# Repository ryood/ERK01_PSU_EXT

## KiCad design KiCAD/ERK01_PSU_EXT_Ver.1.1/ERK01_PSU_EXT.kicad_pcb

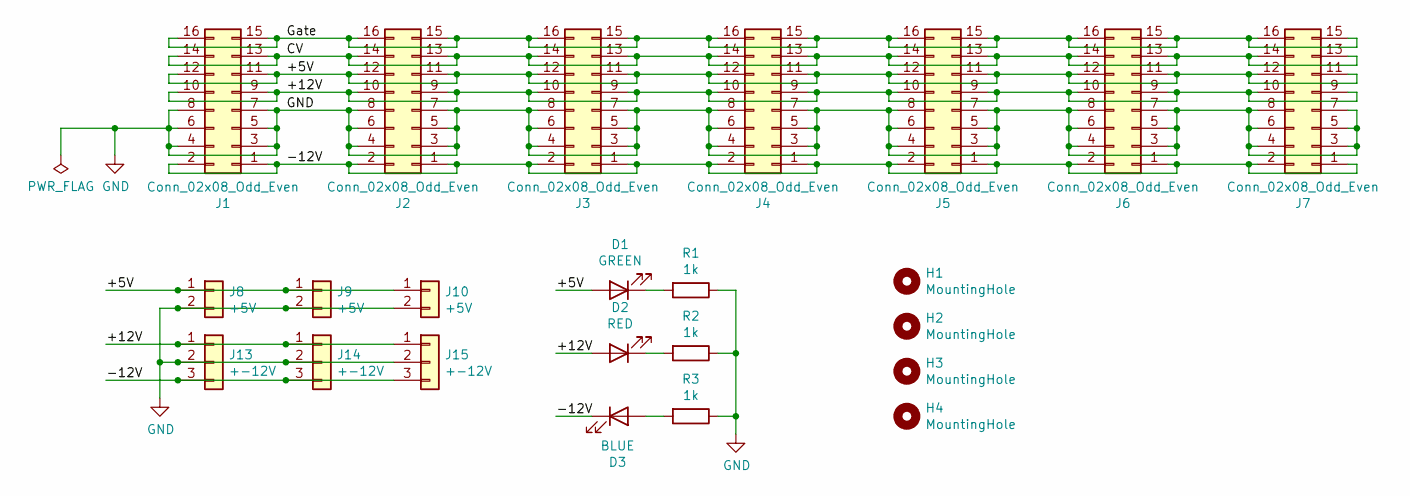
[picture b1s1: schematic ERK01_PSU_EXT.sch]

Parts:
D1: GREEN; LED_D3.0mm
D2: RED; LED_D3.0mm
D3: BLUE; LED_D3.0mm
H1, H2, H3, H4: MountingHole; MountingHole_3.2mm_M3
J1, J2, J3, J4, J5, J6, J7: Conn_02x08_Odd_Even; IDC-Header_2x08_P2.54mm_Vertical
J8, J9, J10: +5V; JST_XH_B2B-XH-A_1x02_P2.50mm_Vertical
J13, J14, J15: +-12V; JST_XH_B3B-XH-A_1x03_P2.50mm_Vertical
R1, R2, R3: 1k; R_Axial_DIN0207_L6.3mm_D2.5mm_P7.62mm_Horizontal

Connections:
/+5V: D1.2 (A), J1.11, J1.12, J2.11, J2.12, J3.11, J3.12, J4.11, J4.12, J5.11, J5.12, J6.11, J6.12, J7.11, J7.12, J8.1, J9.1, J10.1
/+12V: D2.2 (A), J1.9, J1.10, J2.9, J2.10, J3.9, J3.10, J4.9, J4.10, J5.9, J5.10, J6.9, J6.10, J7.9, J7.10, J13.1, J14.1, J15.1
/-12V: D3.1 (K), J1.1, J1.2, J2.1, J2.2, J3.1, J3.2, J4.1, J4.2, J5.1, J5.2, J6.1, J6.2, J7.1, J7.2, J13.3, J14.3, J15.3
/CV: J1.13, J1.14, J2.13, J2.14, J3.13, J3.14, J4.13, J4.14, J5.13, J5.14, J6.13, J6.14, J7.13, J7.14
/Gate: J1.15, J1.16, J2.15, J2.16, J3.15, J3.16, J4.15, J4.16, J5.15, J5.16, J6.15, J6.16, J7.15, J7.16
GND: J1.3, J1.4, J1.5, J1.6, J1.7, J1.8, J2.3, J2.4, J2.5, J2.6, J2.7, J2.8, J3.3, J3.4, J3.5, J3.6, J3.7, J3.8, J4.3, J4.4, J4.5, J4.6, J4.7, J4.8, J5.3, J5.4, J5.5, J5.6, J5.7, J5.8, J6.3, J6.4, J6.5, J6.6, J6.7, J6.8, J7.3, J7.4, J7.5, J7.6, J7.7, J7.8, J8.2, J9.2, J10.2, J13.2, J14.2, J15.2, R1.1, R2.1, R3.1
unnamed: D1.1 (K), R1.2
unnamed: D2.1 (K), R2.2
unnamed: D3.2 (A), R3.2

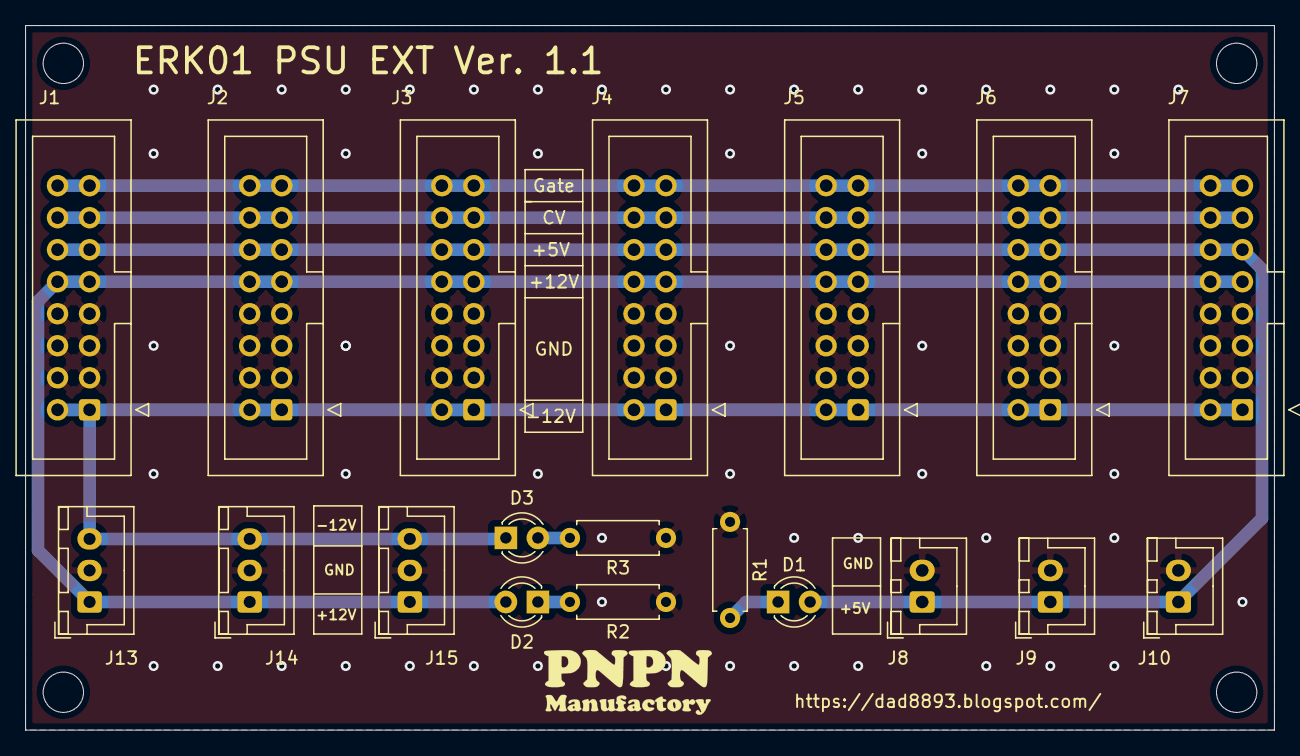
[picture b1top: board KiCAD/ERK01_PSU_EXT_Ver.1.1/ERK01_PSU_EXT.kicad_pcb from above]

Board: 2 copper layers, 99.1 x 55.9 mm, 23 parts (0 on the bottom side), 9 nets.

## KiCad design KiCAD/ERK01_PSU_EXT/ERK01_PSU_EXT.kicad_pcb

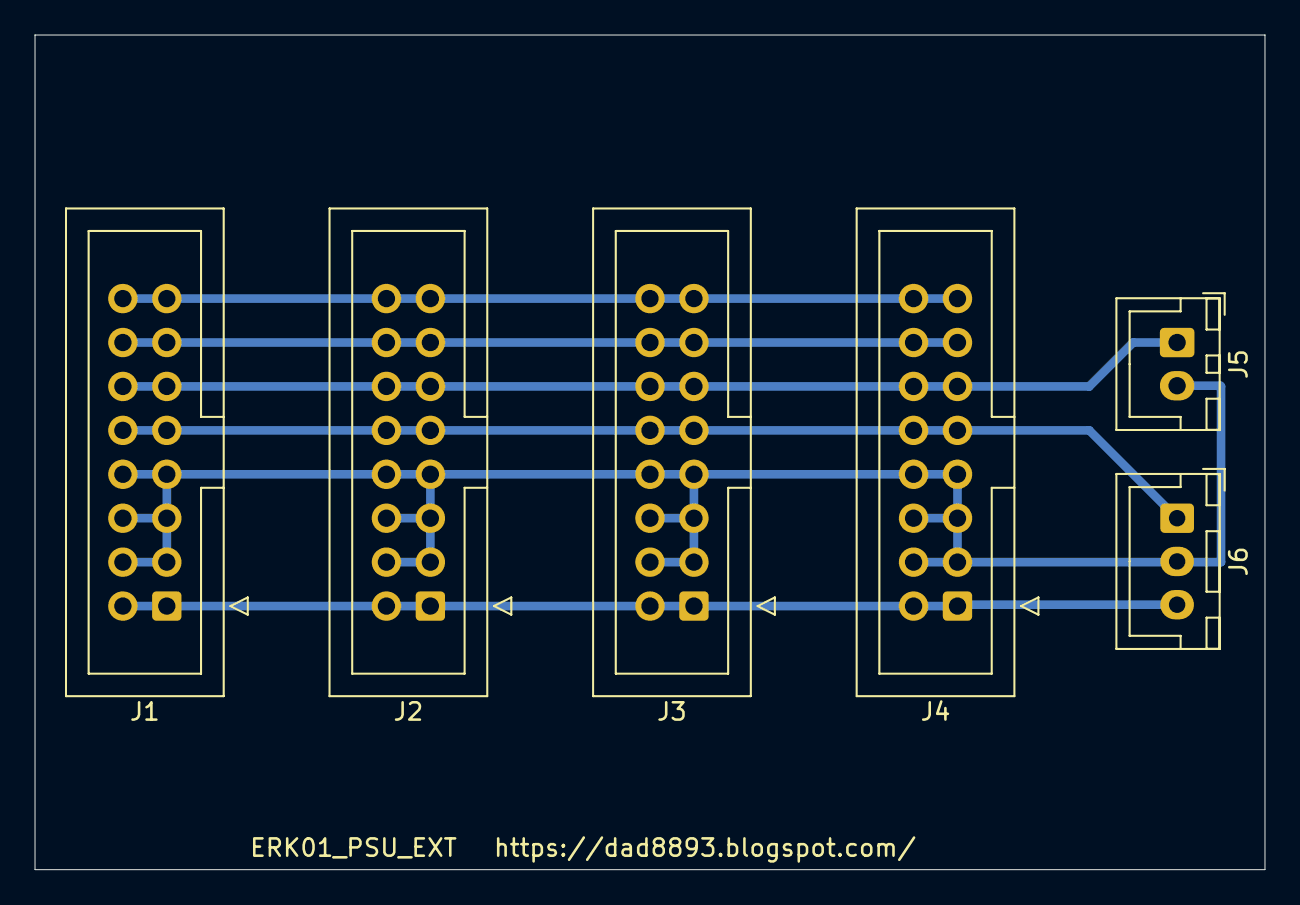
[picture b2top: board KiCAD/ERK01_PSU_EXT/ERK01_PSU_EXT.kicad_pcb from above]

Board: 2 copper layers, 71.1 x 48.3 mm, 6 parts (0 on the bottom side), 6 nets.

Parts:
J1, J2, J3, J4: Conn_02x08_Odd_Even; IDC-Header_2x08_P2.54mm_Vertical
J5: Conn_01x02; JST_XH_B2B-XH-A_1x02_P2.50mm_Vertical
J6: Conn_01x03; JST_XH_B3B-XH-A_1x03_P2.50mm_Vertical

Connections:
/+5V: J1.11, J1.12, J2.11, J2.12, J3.11, J3.12, J4.11, J4.12, J5.1
/+12V: J1.9, J1.10, J2.9, J2.10, J3.9, J3.10, J4.9, J4.10, J6.1
/-12V: J1.1, J1.2, J2.1, J2.2, J3.1, J3.2, J4.1, J4.2, J6.3
/CV: J1.13, J1.14, J2.13, J2.14, J3.13, J3.14, J4.13, J4.14
/Gate: J1.15, J1.16, J2.15, J2.16, J3.15, J3.16, J4.15, J4.16
GND: J1.3, J1.4, J1.5, J1.6, J1.7, J1.8, J2.3, J2.4, J2.5, J2.6, J2.7, J2.8, J3.3, J3.4, J3.5, J3.6, J3.7, J3.8, J4.3, J4.4, J4.5, J4.6, J4.7, J4.8, J5.2, J6.2

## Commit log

2020-09-09 Update: Board Design
2020-12-29 Add: Ver.1.0
2020-12-29 Add: Ver.1.1
2021-03-07 Gerber
2021-03-07 Bug fixed
